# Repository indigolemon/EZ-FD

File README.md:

# EZ-FD
Allow standard PC floppy drives to be used with an Amiga

A small PCB designed to sit between the Amiga motherboard and the floppy drive.
Based on the same idea as the EZ-DF0 that was sold by Eyetech many years ago.

Testing shows it works well, though ATK shows a fluctuating RDY signal.

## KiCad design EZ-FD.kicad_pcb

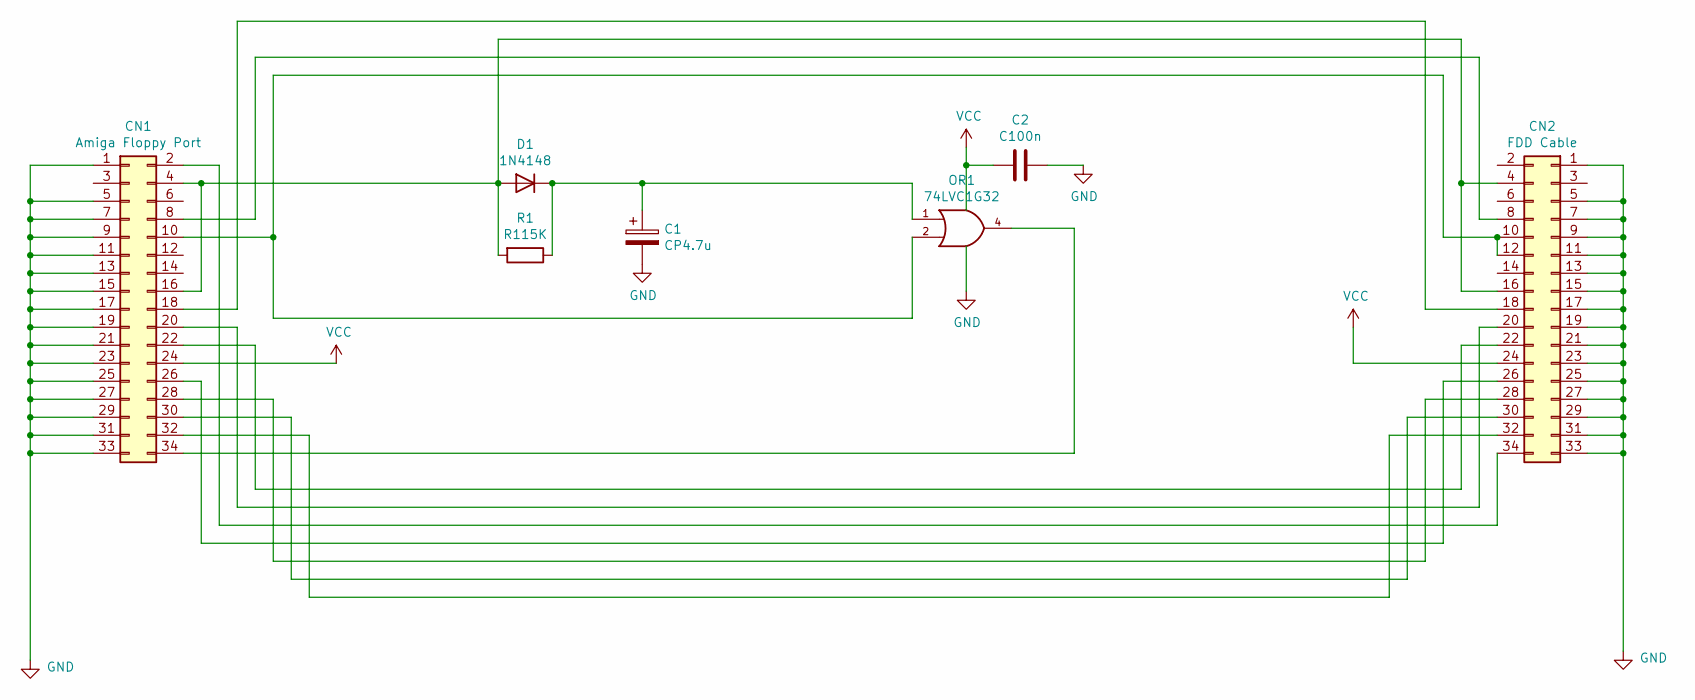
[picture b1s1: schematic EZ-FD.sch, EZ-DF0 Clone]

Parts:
C1: CP4.7u; C_0603_1608Metric_Pad1.05x0.95mm_HandSolder
C2: C100n; C_0603_1608Metric_Pad1.05x0.95mm_HandSolder
CN1: Amiga Floppy Port; PinHeader_2x17_P2.54mm_Vertical
CN2: FDD Cable; PinHeader_2x17_P2.54mm_Vertical
D1: 1N4148; D_0603_1608Metric_Pad1.05x0.95mm_HandSolder
OR1: 74LVC1G32; SOT-23-5_HandSoldering
R1: R115K; R_0603_1608Metric_Pad1.05x0.95mm_HandSolder

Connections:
GND: C1.2, C2.1, CN1.1, CN1.5, CN1.7, CN1.9, CN1.11, CN1.13, CN1.15, CN1.17, CN1.19, CN1.21, CN1.23, CN1.25, CN1.27, CN1.29, CN1.31, CN1.33, CN2.1, CN2.5, CN2.7, CN2.9, CN2.11, CN2.13, CN2.15, CN2.17, CN2.19, CN2.21, CN2.23, CN2.25, CN2.27, CN2.29, CN2.31, CN2.33, OR1.3 (GND)
unnamed: C1.1, D1.1 (K), OR1.1, R1.1
unnamed: CN1.2, CN2.34
unnamed: CN1.8, CN2.8
unnamed: CN1.10, CN2.10, CN2.12, OR1.2
unnamed: CN1.4, CN1.16, CN2.4, CN2.16, D1.2 (A), R1.2
unnamed: CN1.18, CN2.18
unnamed: CN1.20, CN2.20
unnamed: CN1.22, CN2.22
unnamed: CN1.26, CN2.26
unnamed: CN1.28, CN2.28
unnamed: CN1.30, CN2.30
unnamed: CN1.32, CN2.32
unnamed: CN1.34, OR1.4
VCC: C2.2, CN1.24, CN2.24, OR1.5 (VCC)

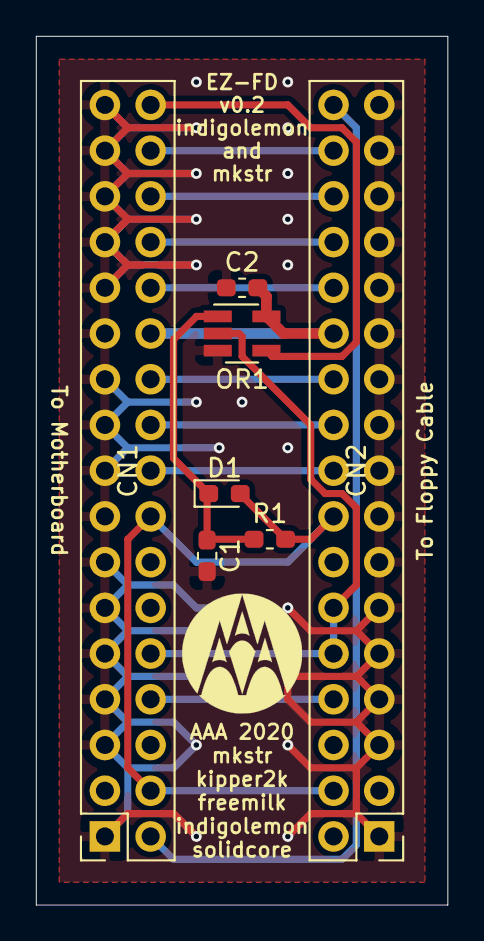
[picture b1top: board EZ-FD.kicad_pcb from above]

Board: 2 copper layers, 22.9 x 48.3 mm, 7 parts (0 on the bottom side), 15 nets.

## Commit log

2022-02-10 Initial commit of all project files
2022-02-10 Cleaned up BOM, removed redundant backup zip
